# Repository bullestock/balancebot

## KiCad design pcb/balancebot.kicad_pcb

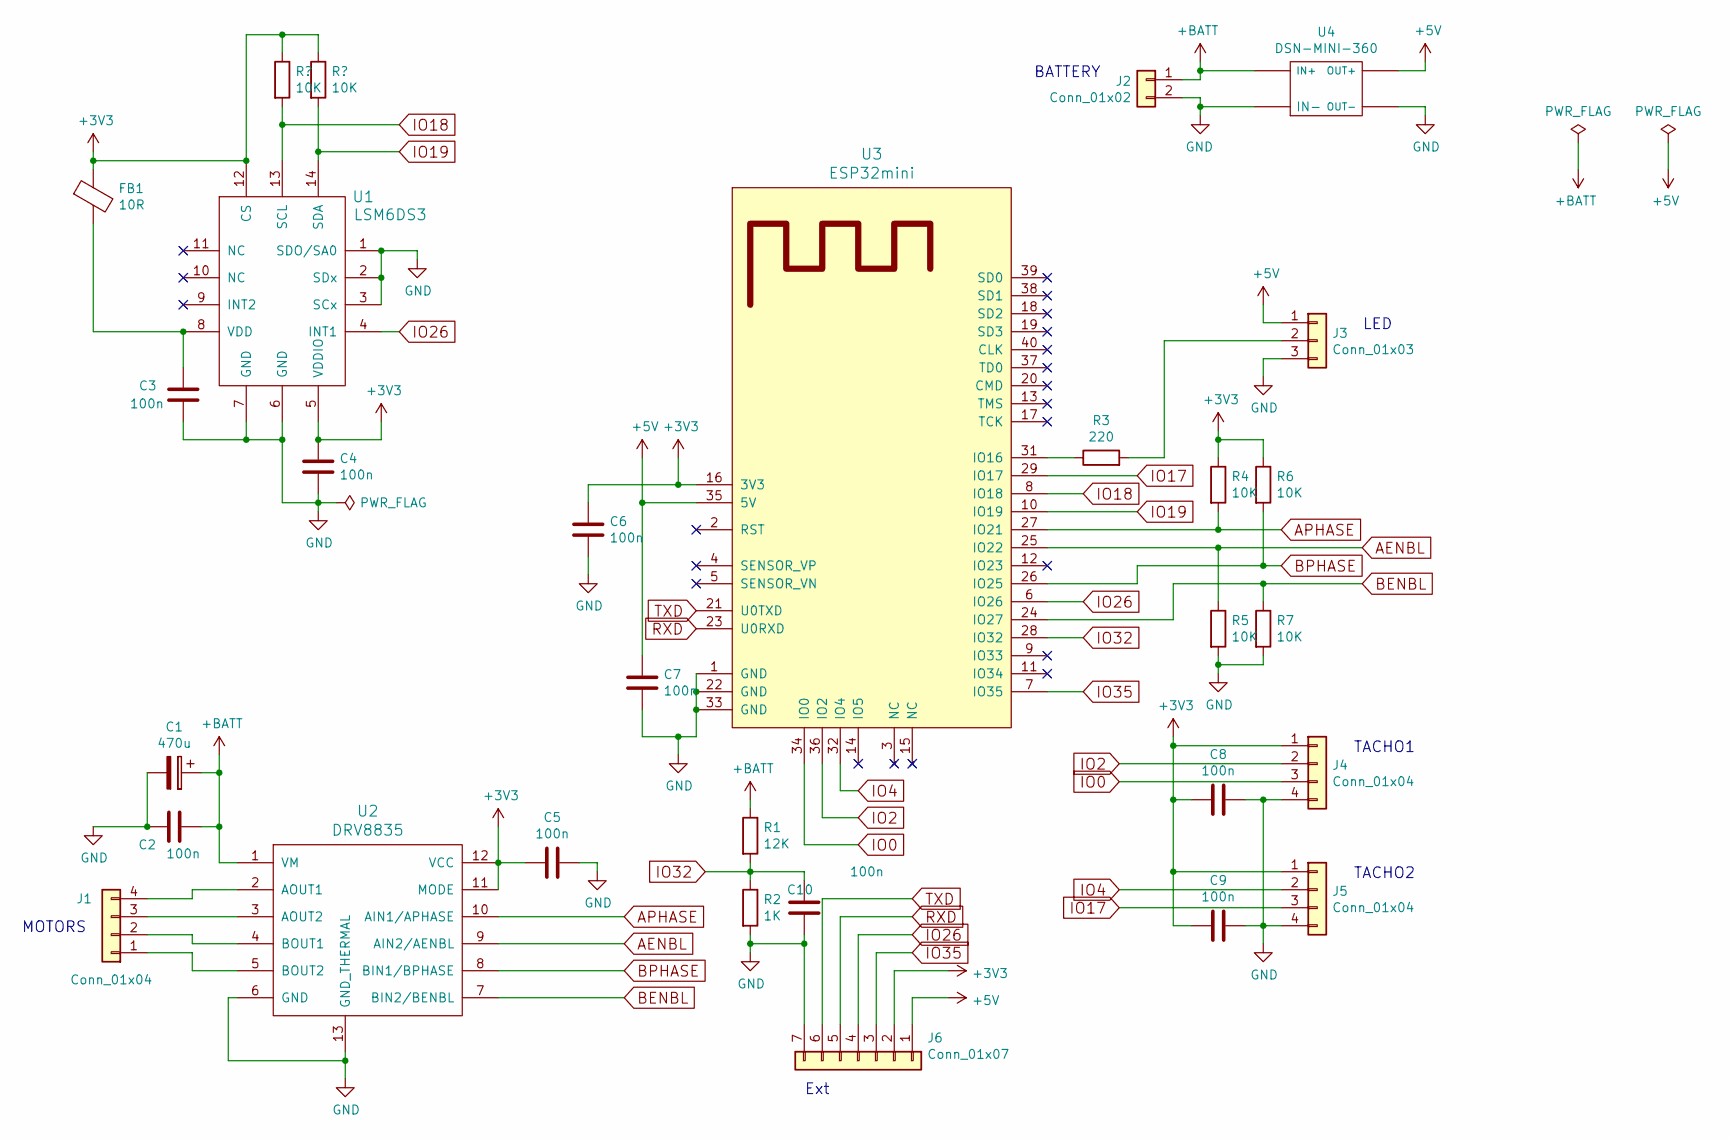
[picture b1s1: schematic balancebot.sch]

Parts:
C1: 470u; CP_Elec_8x10
C2, C3, C4, C5, C6, C7, C8, C9, C10: 100n; C_0603_1608Metric
FB1: 10R; L_0603_1608Metric
J1, J4, J5: Conn_01x04; JST_XH_B04B-XH-A_1x04_P2.50mm_Vertical
J2: Conn_01x02; JST_XH_B02B-XH-A_1x02_P2.50mm_Vertical
J3: Conn_01x03; JST_XH_B03B-XH-A_1x03_P2.50mm_Vertical
J6: Conn_01x07; JST_XH_B07B-XH-A_1x07_P2.50mm_Vertical
R1: 12K; R_0603_1608Metric
R2: 1K; R_0603_1608Metric
R3: 220; R_0603_1608Metric
R4, R5, R6, R7: 10K; R_0603_1608Metric
U1: LSM6DS3; LGA-14L
U2: DRV8835; WSON-12
U3: ESP32mini
U4: DSN-MINI-360

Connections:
+3V3: C4.1, C5.2, C6.1, C8.2, C9.2, FB1.1, J4.1, J5.1, J6.2, R4.1, R6.1, U1.5 (VDDIO), U1.12 (CS), U2.11 (MODE), U2.12 (VCC), U3.16 (3V3)
+5V: C7.1, J3.1, J6.1, U3.35 (5V), U4.OUT+
+BATT: C1.1, C2.1, J2.1, R1.1, U2.1 (VM), U4.IN+
AENBL: R5.1, U2.9 (AIN2/AENBL), U3.25 (IO22)
APHASE: R4.2, U2.10 (AIN1/APHASE), U3.27 (IO21)
BENBL: R7.1, U2.7 (BIN2/BENBL), U3.24 (IO27)
BPHASE: R6.2, U2.8 (BIN1/BPHASE), U3.26 (IO25)
GND: C1.2, C2.2, C3.2, C4.2, C5.1, C6.2, C7.2, C8.1, C9.1, C10.2, J2.2, J3.3, J4.4, J5.4, J6.7, R2.2, R5.2, R7.2, U1.1 (SDO/SA0), U1.2 (SDx), U1.3 (SCx), U1.6 (GND), U1.7 (GND), U2.6 (GND), U2.13 (GND_THERMAL), U3.1 (GND), U3.22 (GND), U3.33 (GND), U4.IN-, U4.OUT-
IO0: J4.3, U3.34 (IO0)
IO2: J4.2, U3.36 (IO2)
IO4: J5.2, U3.32 (IO4)
IO17: J5.3, U3.29 (IO17)
IO18: U1.13 (SCL), U3.8 (IO18)
IO19: U1.14 (SDA), U3.10 (IO19)
IO26: J6.4, U1.4 (INT1), U3.6 (IO26)
IO32: C10.1, R1.2, R2.1, U3.28 (IO32)
IO35: J6.3, U3.7 (IO35)
unnamed: C3.1, FB1.2, U1.8 (VDD)
unnamed: J1.1, U2.5 (BOUT2)
unnamed: J1.2, U2.4 (BOUT1)
unnamed: J1.3, U2.3 (AOUT2)
unnamed: J1.4, U2.2 (AOUT1)
unnamed: J3.2, R3.2
unnamed: R3.1, U3.31 (IO16)
RXD: J6.5, U3.23 (U0RXD)
TXD: J6.6, U3.21 (U0TXD)

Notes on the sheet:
LED
TACHO1
TACHO2
MOTORS
BATTERY
Ext

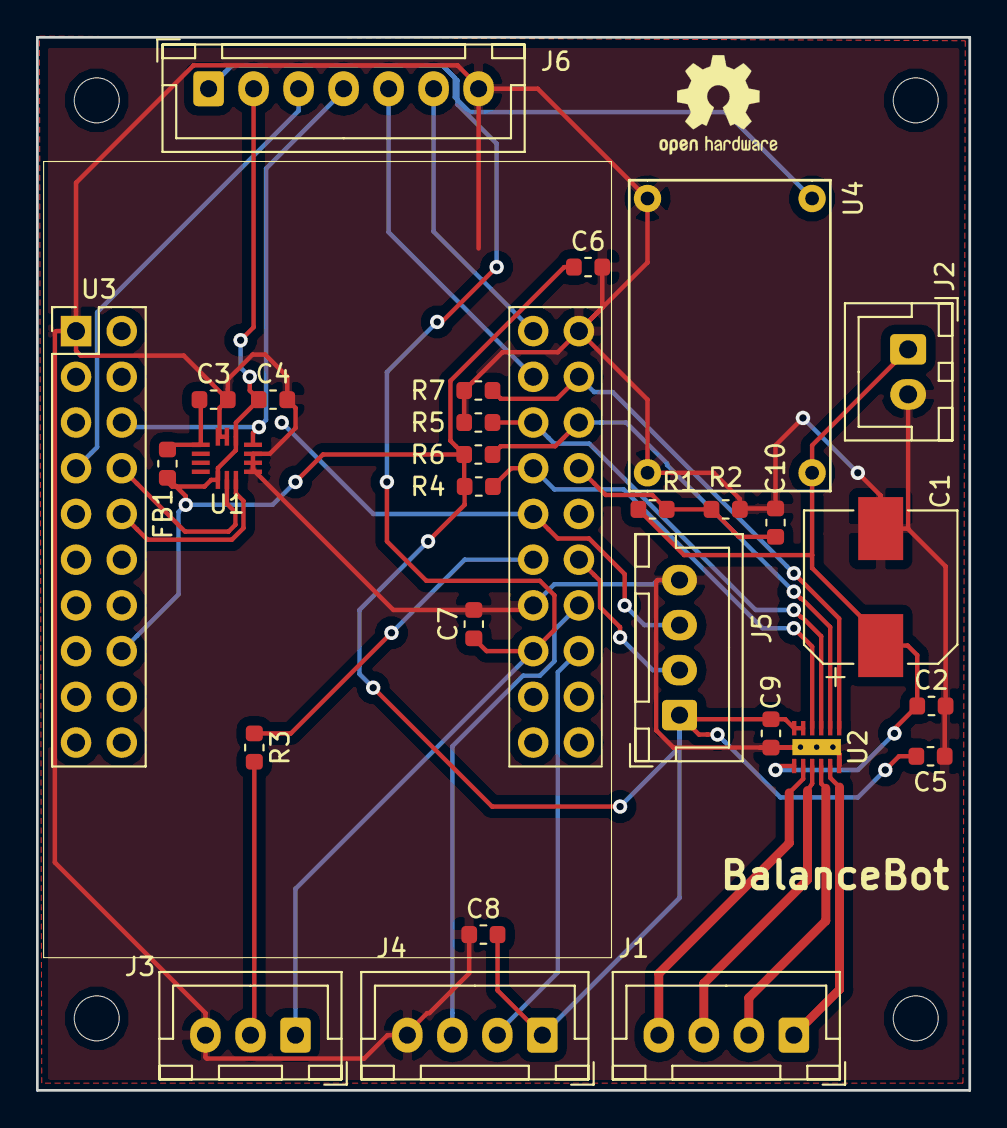
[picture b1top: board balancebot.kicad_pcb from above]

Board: 2 copper layers, 51.8 x 58.5 mm, 28 parts (0 on the bottom side), 26 nets.

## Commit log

2018-03-23 Test.
2018-04-07 Add case.
2018-04-07 Increase depth and width.
2018-04-07 Fix minor bugs.
2018-04-08 Make room for wheels.
2018-04-10 Ungroup to make LasaurApp work properly. Add battery support.
2018-04-13 Fix size of wheel covers.
2018-04-13 Add LED test code.
2018-04-14 Add motor task.
2018-04-14 Control both motors.
2018-04-17 Refactor.
2018-04-17 Remove debug.
2018-04-18 Add encoder test code.
2018-04-18 Add second encoder.
2018-06-17 Read WHO_AM_I register from LSM6DS3.
2018-06-19 Implement IMU config and register read.
2018-06-23 Adding stuff.
2018-06-24 Fix motor B direction.
2018-06-26 Add WiFi setup.
2018-06-30 Add WebSocket test code.
2018-06-30 Port ESPway web interface.
2018-07-17 Implement NVS storage.
2018-07-21 Add battery task; enable main task again.
2018-07-21 Move battery_task() to main.cpp.
2018-07-21 Fix battery scale factor.
2018-07-21 Clean up API and code.
2018-07-21 Fix indent, etc.
2018-07-21 Fix handling of PID coefficients.
2018-07-21 Fix more conversion issues.
2018-08-03 Increase I2C frequency to 1 MHz.
2018-08-04 Fix race condition.
2018-08-05 Improve error reporting.
2018-08-05 Remove unused code; turn eyes yellow on startup.
2018-10-21 Add schematic.
2018-10-24 Fix ESP32 footprint.
2018-10-24 Invert axis.
2018-10-24 Debug update frequency.
2018-10-26 Complete routing.
2018-10-26 Make pretty.
2018-10-27 Update ESP32 footprint; make motor traces wider.
2018-10-27 Finalize PCB.
2018-10-28 Change WSON-12 via to 0.3 mm.
2019-03-30 Use correct pins.
2019-05-28 Start using LSM6DS3 driver from mjstn/MarkWorldCodeModules.
2019-05-29 Use MarkWorld driver.
2019-05-29 Add console commands.
2019-05-31 Make motor control work.
2019-06-05 Show averaged IMU readings.
2019-06-05 Remove delay.
2019-06-08 Add LED test.
2019-06-08 Fix NUL bytes in HTML/JS.
2019-06-08 Add named states.
2019-06-08 Fancy colours.
2019-06-08 Add headers.
2019-06-08 Fix detection of wound up state.
2019-06-15 Add battery check.
2019-07-17 Omit #define in output.
2019-07-17 Add set_color_right().
2019-07-17 Disable motors when running on USB power.
2019-07-17 Add disable_motors().
2019-07-27 Fix LSM6DS3 settings to match espway project.
2019-07-27 Playing around with a simpler PID algorithm.
2019-07-31 Fix forward axis direction.
2019-07-31 Cleanup.
2019-07-31 New case with round top.
2019-07-31 Ignore.
2019-07-31 Add missing file.
2019-07-31 Add frontend source.
2019-08-01 Fix paths.
2019-08-02 Fix naming.
2019-08-07 Allow for level conversion pixel.
2019-08-07 Use only predefined colours for LED test.
2019-08-07 Connect to bot via WebSocket.
2019-08-07 Update.
2019-08-07 Increase size.
2019-08-07 Disable battery cutoff.
2019-08-07 Improve shutdown.
2019-08-07 Save BT address to a file.
2019-08-09 Add WebSocket skeleton.
2019-08-09 Simplify.
2019-08-10 First working version.
2019-08-14 Use display, add automatic retry.
2019-08-14 Show wired IP on line 0.
2019-08-14 Move Display to separate file; show battery voltage.
2019-08-31 Add systemd unit file.
2019-08-31 Use separate scaling factors for steering and speed.
2019-09-01 Reset steering after a period with no user input.
2019-09-17 Fix typo.
2019-09-21 Reset steering on Wiiboard inactivity.
2019-09-28 Use auth for wifi link.
2019-09-28 Move WiFi pass to secrets.py
2019-10-25 Battery box, initial
2019-11-02 Bump webpack-dev-server from 2.3.0 to 3.1.11 in /frontend
    Bumps [webpack-dev-server](https://github.com/webpack/webpack-dev-server) from 2.3.0 to 3.1.11.
    - [Release notes](https://github.com/webpack/webpack-dev-server/releases)
    - [Changelog](https://github.com/webpack/webpack-dev-server/blob/master/CHANGELOG.md)
    - [Commits](https://github.com/webpack/webpack-dev-server/compare/v2.3.0...v3.1.11)
2019-11-16 Add acrylic part.
2019-11-17 Start new case design.
2019-11-17 Fix placement of bottom slots.
2019-11-17 Remove junk.
2019-11-17 Add mountplate.
2019-11-17 Center switch.
2019-11-17 Add holes for battery compartment sides.
2019-12-25 Update for new ESP-IDF.
2019-12-25 Fix orientation.
2019-12-27 Remove old case parts.
2019-12-29 Fix width.
2019-12-29 Increase depth of top cutouts.
2020-01-04 First botched attempt.
2020-01-04 Fix plug orientation.
2020-01-04 Reduce width of lid supports.
2020-01-04 Add front lid support.
2020-01-11 Do more tweaks.
2020-01-11 Fix length.
2020-01-11 Make battery fit tighter.
2020-01-11 Add indents for lid.
2020-01-11 Rework LED driver.
2020-01-11 Complete edge part.
2020-01-12 Fix plug cutout.
2020-01-12 First attempt.
2020-01-18 Add hole.
2021-05-09 Get PID coefficients on startup.
2021-05-09 Complete script.
2021-05-14 Rename.
2021-05-14 Update for ESP-IDF 4.2.1.
2021-05-15 Update WiFi code; put password in config.
2021-05-15 Send battery message less often.
2021-05-15 Fix bugs.
2021-05-16 Make restart after fall/windup work; use ref arguments instead of pointer args.
2021-05-19 Make reset button work.
2021-05-19 Read WiFi password from environment.
2021-05-20 Update for ESP-IDF 4.3.
2021-05-20 Refactor based on rotary_encoder example.
2021-05-20 Enable encoder task.
2021-09-08 Fix encoder handling bugs.
2021-09-08 Show speed and distance.
